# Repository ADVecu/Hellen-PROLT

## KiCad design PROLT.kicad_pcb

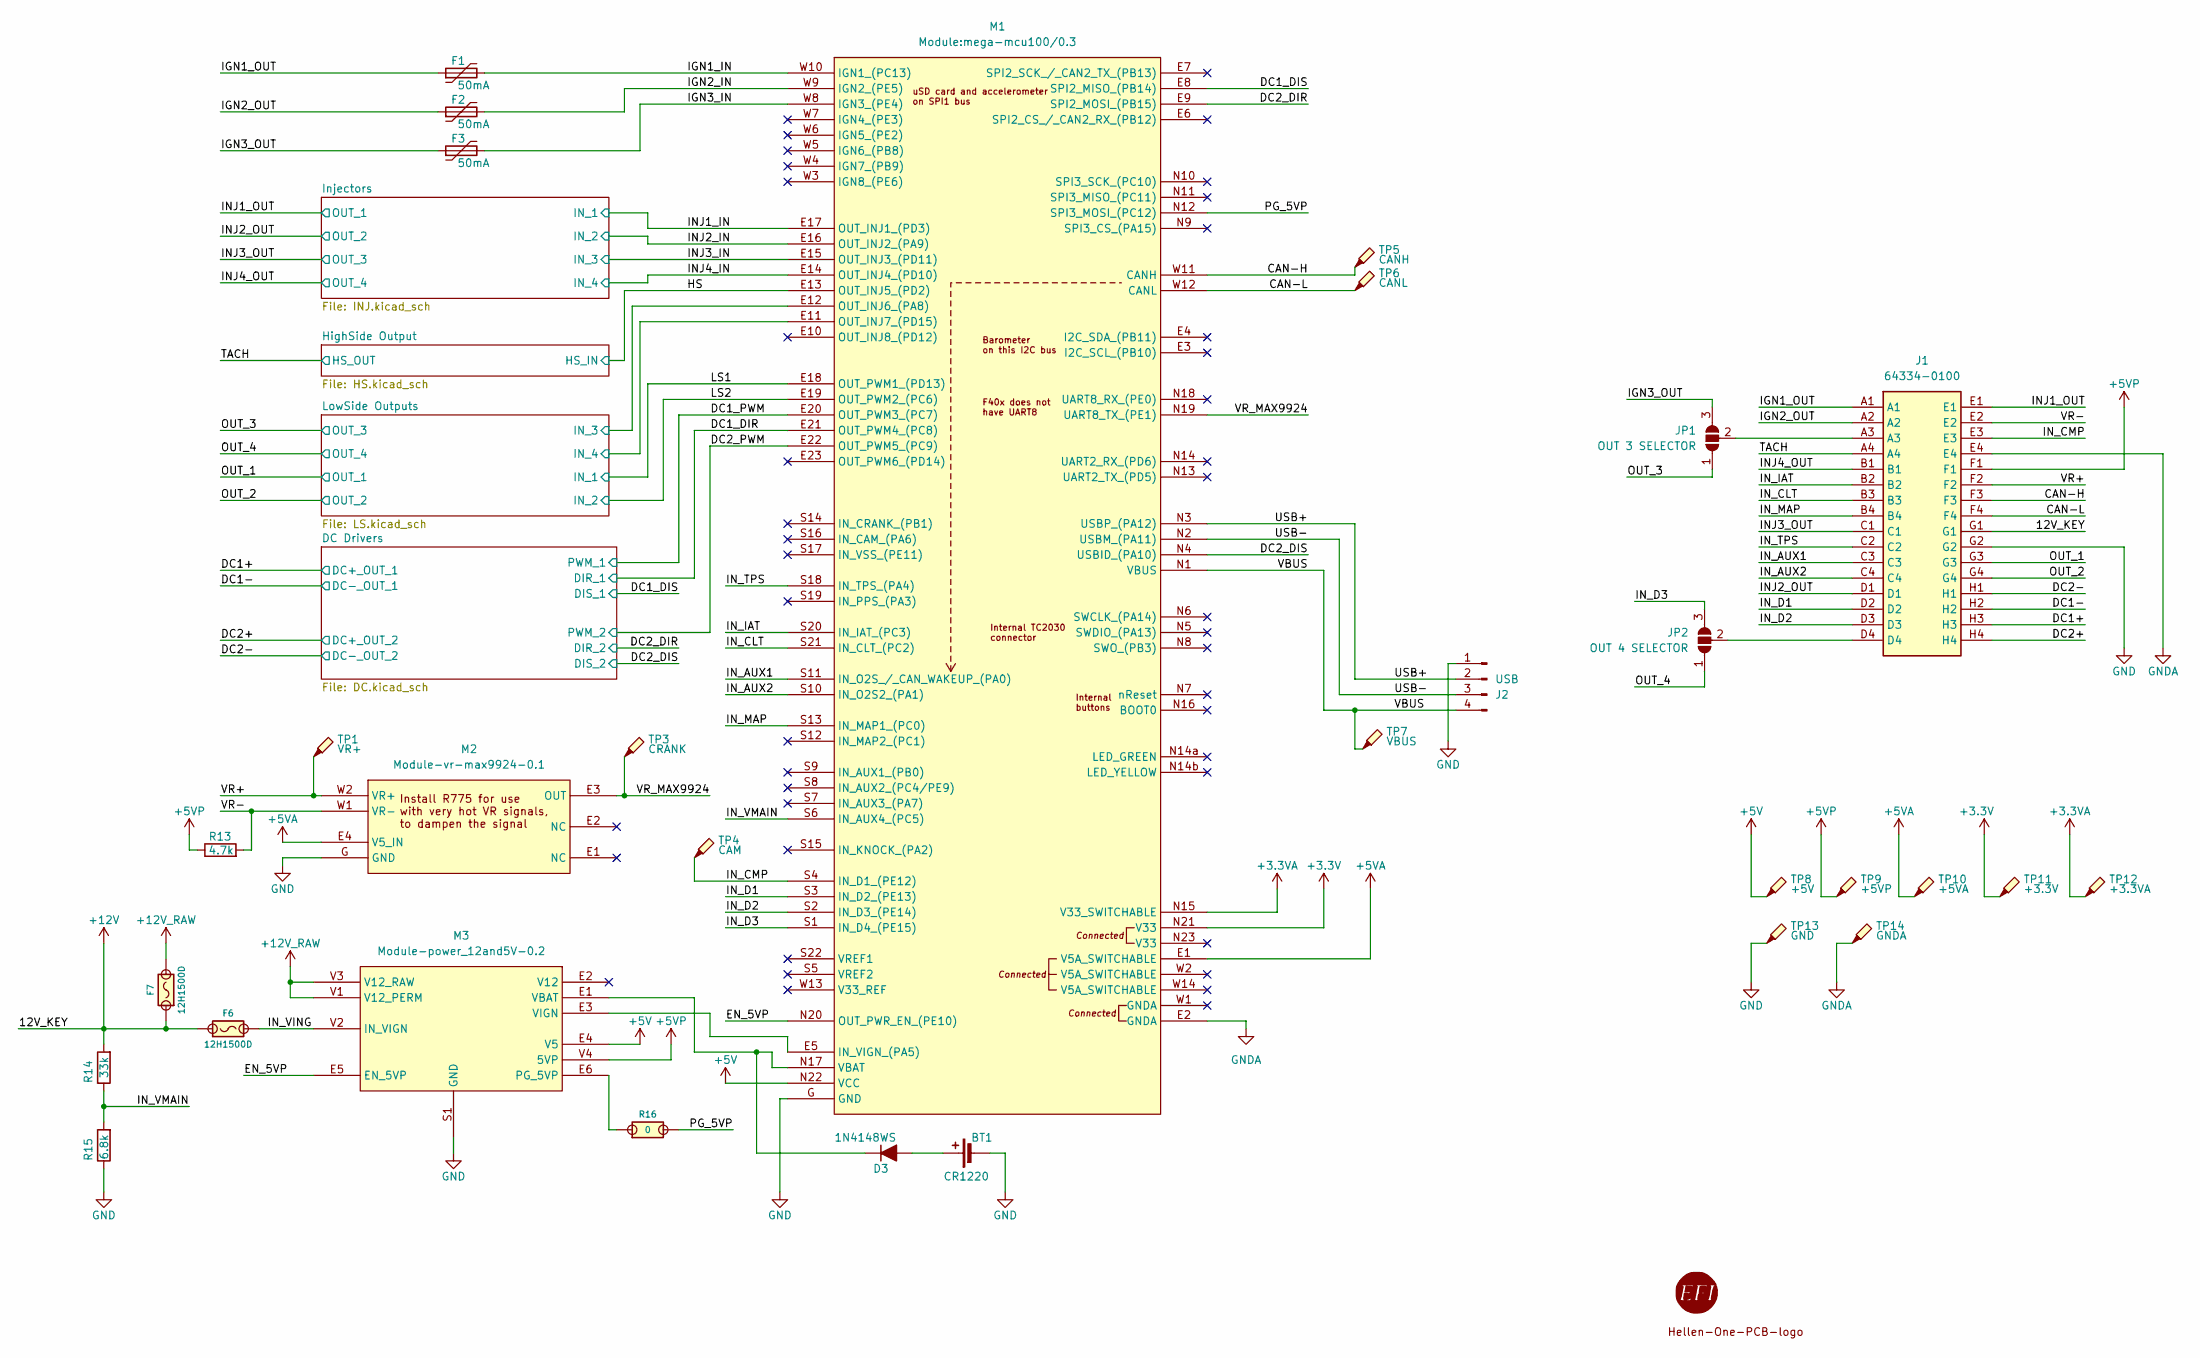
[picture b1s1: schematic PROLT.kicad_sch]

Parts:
BT1: CR1220; CR1220-2; LCSC C70381
D3: 1N4148WS; SOD-323; LCSC C2128
F1, F2, F3: 50mA; Fuse_0603_1608Metric; LCSC C369141
F6, F7: 12H1500D; PAD-1206-PAD; LCSC C182446
G1: RUSEFI_LOGO; rusefi_logo
G2: LOGO
J1: 64334-0100; 643340100; Mouser Part Number 538-64334-0100
J2: USB; JST_PH_B4B-PH-K_1x04_P2.00mm_Vertical; LCSC C5305780
JP1: OUT 3 SELECTOR; SolderJumper-3_P2.0mm_Open_TrianglePad1.0x1.5mm
JP2: OUT 4 SELECTOR; SolderJumper-3_P2.0mm_Open_TrianglePad1.0x1.5mm
M1: Module:mega-mcu100/0.3; mega-mcu100
M2: Module-vr-max9924-0.1; vr-max9924
M3: Module-power_12and5V-0.2; power_12and5V
R13: 4.7k; R0603; LCSC C23162
R14: 33k; R0603; LCSC C4216
R15: 6.8k; R0603; LCSC C23212
R16: 0; PAD-0805-PAD; LCSC C17477
TP1: VR+; TestPoint_Pad_D1.0mm
TP3: CRANK; TestPoint_Pad_D1.0mm
TP4: CAM; TestPoint_Pad_D1.0mm
TP5: CANH; TestPoint_Pad_D1.0mm
TP6: CANL; TestPoint_Pad_D1.0mm
TP7: VBUS; TestPoint_Pad_D1.0mm
TP8: +5V; TestPoint_Pad_D1.0mm
TP9: +5VP; TestPoint_Pad_D1.0mm
TP10: +5VA; TestPoint_Pad_D1.0mm
TP11: +3.3V; TestPoint_Pad_D1.0mm
TP12: +3.3VA; TestPoint_Pad_D1.0mm
TP13: GND; TestPoint_Pad_D2.0mm
TP14: GNDA; TestPoint_Pad_D1.0mm

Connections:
+3.3V: M1.N21 (V33), TP11.1; also elsewhere on the board
+3.3VA: M1.N15 (V33_SWITCHABLE), TP12.1
+5V: M1.N22 (VCC), M3.E4 (V5), TP8.1
+5VA: M1.E1 (V5A_SWITCHABLE), M2.E4 (V5_IN), TP10.1
+5VP: J1.F1, M3.V4 (5VP), R13.1, TP9.1
+12V: F6.1, F7.1, J1.G1, R14.2; also elsewhere on the board
+12V_RAW: F7.2, M3.V1 (V12_PERM), M3.V3 (V12_RAW); also elsewhere on the board
/CAN-H: J1.F3, M1.W11 (CANH), TP5.1
/CAN-L: J1.F4, M1.W12 (CANL), TP6.1
/DC1+: J1.H3; also elsewhere on the board
/DC1-: J1.H2; also elsewhere on the board
/DC1_DIR: M1.E21 (OUT_PWM4_(PC8)); also elsewhere on the board
/DC1_DIS: M1.E8 (SPI2_MISO_(PB14)); also elsewhere on the board
/DC1_PWM: M1.E20 (OUT_PWM3_(PC7)); also elsewhere on the board
/DC2+: J1.H4; also elsewhere on the board
/DC2-: J1.H1; also elsewhere on the board
/DC2_DIR: M1.E9 (SPI2_MOSI_(PB15)); also elsewhere on the board
/DC2_DIS: M1.N4 (USBID_(PA10)); also elsewhere on the board
/DC2_PWM: M1.E22 (OUT_PWM5_(PC9)); also elsewhere on the board
/EN_5VP: M1.N20 (OUT_PWR_EN_(PE10)), M3.E5 (EN_5VP)
/HS: M1.E13 (OUT_INJ5_(PD2)); also elsewhere on the board
/IGN1_IN: F1.2, M1.W10 (IGN1_(PC13))
/IGN1_OUT: F1.1, J1.A1
/IGN2_IN: F2.2, M1.W9 (IGN2_(PE5))
/IGN2_OUT: F2.1, J1.A2
/IGN3_IN: F3.2, M1.W8 (IGN3_(PE4))
/IGN3_OUT: F3.1, JP1.3 (B)
/INJ1_IN: M1.E17 (OUT_INJ1_(PD3)); also elsewhere on the board
/INJ1_OUT: J1.E1; also elsewhere on the board
/INJ2_IN: M1.E16 (OUT_INJ2_(PA9)); also elsewhere on the board
/INJ2_OUT: J1.D1; also elsewhere on the board
/INJ3_IN: M1.E15 (OUT_INJ3_(PD11)); also elsewhere on the board
/INJ3_OUT: J1.C1; also elsewhere on the board
/INJ4_IN: M1.E14 (OUT_INJ4_(PD10)); also elsewhere on the board
/INJ4_OUT: J1.B1; also elsewhere on the board
/IN_AUX1: J1.C3, M1.S11 (IN_O2S_/_CAN_WAKEUP_(PA0))
/IN_AUX2: J1.C4, M1.S10 (IN_O2S2_(PA1))
/IN_CLT: J1.B3, M1.S21 (IN_CLT_(PC2))
/IN_CMP: J1.E3, M1.S4 (IN_D1_(PE12)), TP4.1
/IN_D1: J1.D2, M1.S3 (IN_D2_(PE13))
/IN_D2: J1.D3, M1.S2 (IN_D3_(PE14))
/IN_D3: JP2.3 (B), M1.S1 (IN_D4_(PE15))
/IN_IAT: J1.B2, M1.S20 (IN_IAT_(PC3))
/IN_MAP: J1.B4, M1.S13 (IN_MAP1_(PC0))
/IN_TPS: J1.C2, M1.S18 (IN_TPS_(PA4))
/IN_VING: F6.2, M3.V2 (IN_VIGN)
/IN_VMAIN: M1.S6 (IN_AUX4_(PC5)), R14.1, R15.2
/LS1: M1.E18 (OUT_PWM1_(PD13)); also elsewhere on the board
/LS2: M1.E19 (OUT_PWM2_(PC6)); also elsewhere on the board
/LowSide Outputs/IN_3: M1.E12 (OUT_INJ6_(PA8)); also elsewhere on the board
/LowSide Outputs/IN_4: M1.E11 (OUT_INJ7_(PD15)); also elsewhere on the board
/OUT_1: J1.G3; also elsewhere on the board
/OUT_2: J1.G4; also elsewhere on the board
/OUT_3: JP1.1 (A); also elsewhere on the board
/OUT_4: JP2.1 (A); also elsewhere on the board
/PG_5VP: M1.N12 (SPI3_MOSI_(PC12)), R16.2
/TACH: J1.A4; also elsewhere on the board
/USB+: J2.2, M1.N3 (USBP_(PA12))
/USB-: J2.3, M1.N2 (USBM_(PA11))
/VBUS: J2.4, M1.N1 (VBUS), TP7.1
/VR+: J1.F2, M2.W2 (VR+), TP1.1
/VR-: J1.E2, M2.W1 (VR-), R13.2
/VR_MAX9924: M1.N19 (UART8_TX_(PE1)), M2.E3 (OUT), TP3.1
GND: BT1.2 (-), J1.G2, J2.1, M1.G (GND), M2.G (GND), M3.S1 (GND), R15.1, TP13.1; also elsewhere on the board
GNDA: J1.E4, M1.E2 (GNDA), TP14.1
unnamed: BT1.1 (+), D3.2 (A)
unnamed: D3.1 (K), M1.N17 (VBAT), M3.E1 (VBAT)
unnamed: J1.A3, JP1.2 (C)
unnamed: J1.D4, JP2.2 (C)
unnamed: M1.E5 (IN_VIGN_(PA5)), M3.E3 (VIGN)
unnamed: M3.E6 (PG_5VP), R16.1

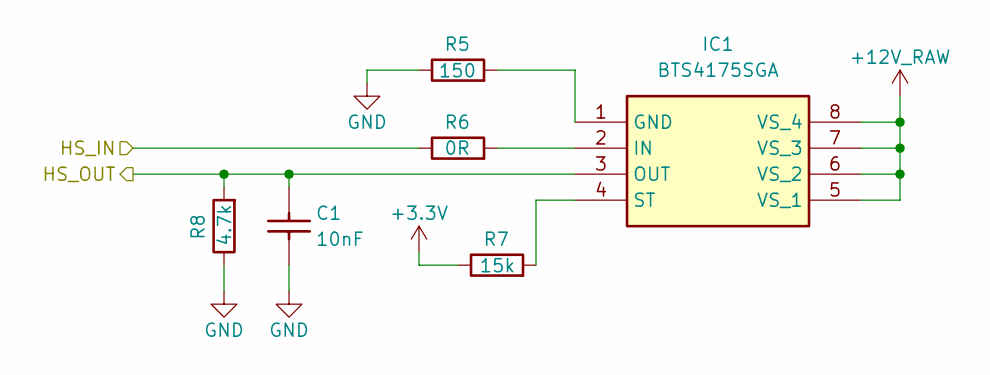
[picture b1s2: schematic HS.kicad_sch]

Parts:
C1: 10nF; C0603; LCSC C57112
IC1: BTS4175SGA; SOIC127P600X175-8N; Mouser Part Number 726-BTS4175SGA
R5: 150; R0603; LCSC C325755
R6: 0R; R0603; LCSC C2770782
R7: 15k; R0603; LCSC C881094
R8: 4.7k; R0603; LCSC C23162

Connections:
+3.3V: R7.1; also elsewhere on the board
+12V_RAW: IC1.5 (VS_1), IC1.6 (VS_2), IC1.7 (VS_3), IC1.8 (VS_4); also elsewhere on the board
/HS: R6.1; also elsewhere on the board
/TACH: C1.2, IC1.3 (OUT), R8.2; also elsewhere on the board
GND: C1.1, R5.1, R8.1; also elsewhere on the board
unnamed: IC1.1 (GND), R5.2
unnamed: IC1.2 (IN), R6.2
unnamed: IC1.4 (ST), R7.2

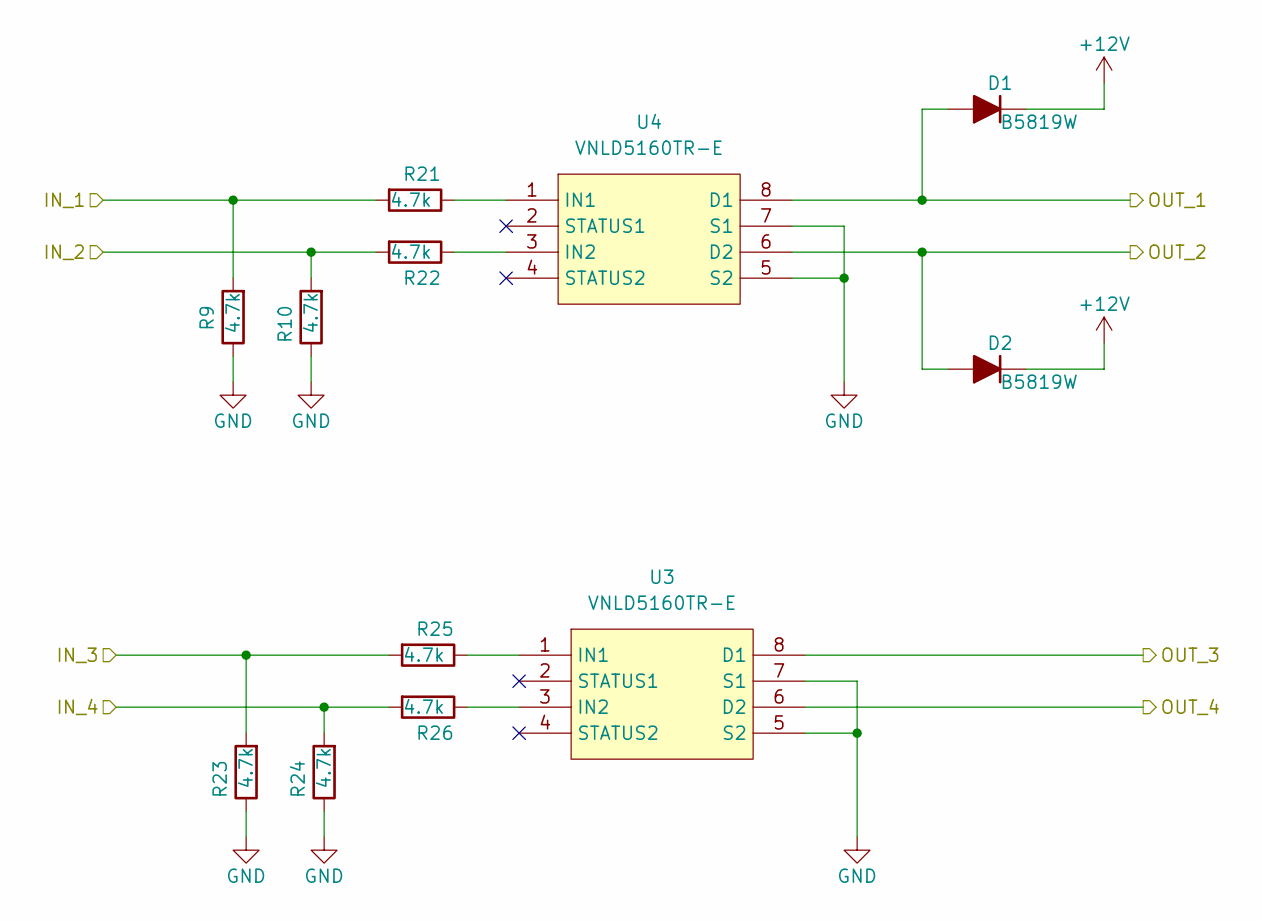
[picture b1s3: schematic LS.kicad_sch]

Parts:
D1, D2: B5819W; SOD-123; LCSC C8598
R9, R10, R21, R22, R23, R24, R25, R26: 4.7k; R0603; LCSC C23162
U3, U4: VNLD5160TR-E; SOIC-8_3.9x4.9mm_P1.27mm; LCSC C377942

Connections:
+12V: D1.1 (K), D2.1 (K); also elsewhere on the board
/LS1: R9.2, R21.2; also elsewhere on the board
/LS2: R10.2, R22.2; also elsewhere on the board
/LowSide Outputs/IN_3: R23.2, R25.2; also elsewhere on the board
/LowSide Outputs/IN_4: R24.2, R26.2; also elsewhere on the board
/OUT_1: D1.2 (A), U4.8 (D1); also elsewhere on the board
/OUT_2: D2.2 (A), U4.6 (D2); also elsewhere on the board
/OUT_3: U3.8 (D1); also elsewhere on the board
/OUT_4: U3.6 (D2); also elsewhere on the board
GND: R9.1, R10.1, R23.1, R24.1, U3.5 (S2), U3.7 (S1), U4.5 (S2), U4.7 (S1); also elsewhere on the board
unnamed: R25.1, U3.1 (IN1)
unnamed: R26.1, U3.3 (IN2)
unnamed: R21.1, U4.1 (IN1)
unnamed: R22.1, U4.3 (IN2)

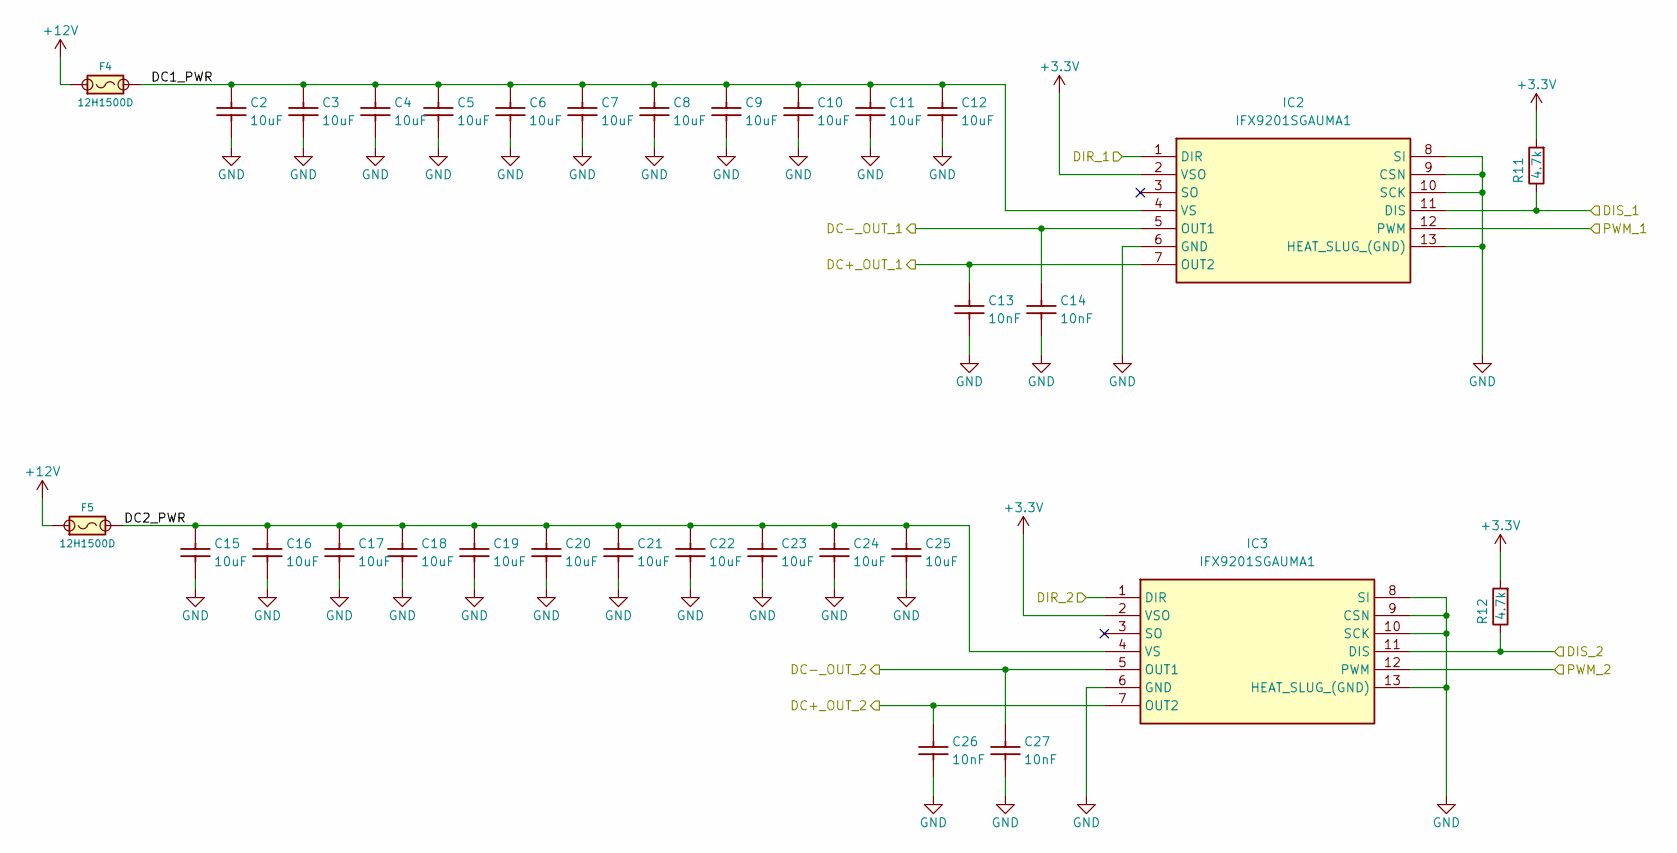
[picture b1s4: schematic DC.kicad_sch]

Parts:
C2, C3, C4, C5, C6, C7, C8, C9, C10, C11, C12, C15, C16, C17, C18, C19, C20, C21, C22, C23, C24, C25: 10uF; C0805; LCSC C15850
C13, C14, C26, C27: 10nF; C0603; LCSC C57112
F4, F5: 12H1500D; PAD-1206-PAD; LCSC C182446
IC2, IC3: IFX9201SGAUMA1; PG-DSO-12-17; Mouser Part Number 726-IFX9201SGAUMA1
R11, R12: 4.7k; R0603; LCSC C23162

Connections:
+3.3V: IC2.2 (VSO), IC3.2 (VSO), R11.2, R12.2; also elsewhere on the board
+12V: F4.1, F5.1; also elsewhere on the board
/DC1+: C13.2, IC2.7 (OUT2); also elsewhere on the board
/DC1-: C14.2, IC2.5 (OUT1); also elsewhere on the board
/DC1_DIR: IC2.1 (DIR); also elsewhere on the board
/DC1_DIS: IC2.11 (DIS), R11.1; also elsewhere on the board
/DC1_PWM: IC2.12 (PWM); also elsewhere on the board
/DC2+: C26.2, IC3.7 (OUT2); also elsewhere on the board
/DC2-: C27.2, IC3.5 (OUT1); also elsewhere on the board
/DC2_DIR: IC3.1 (DIR); also elsewhere on the board
/DC2_DIS: IC3.11 (DIS), R12.1; also elsewhere on the board
/DC2_PWM: IC3.12 (PWM); also elsewhere on the board
/DC Drivers/DC1_PWR: C2.2, C3.2, C4.2, C5.2, C6.2, C7.2, C8.2, C9.2, C10.2, C11.2, C12.2, F4.2, IC2.4 (VS)
/DC Drivers/DC2_PWR: C15.2, C16.2, C17.2, C18.2, C19.2, C20.2, C21.2, C22.2, C23.2, C24.2, C25.2, F5.2, IC3.4 (VS)
GND: C2.1, C3.1, C4.1, C5.1, C6.1, C7.1, C8.1, C9.1, C10.1, C11.1, C12.1, C13.1, C14.1, C15.1, C16.1, C17.1, C18.1, C19.1, C20.1, C21.1, C22.1, C23.1, C24.1, C25.1, C26.1, C27.1, IC2.6 (GND), IC2.8 (SI), IC2.9 (CSN), IC2.10 (SCK), IC2.13 (HEAT_SLUG_(GND)), IC3.6 (GND), IC3.8 (SI), IC3.9 (CSN), IC3.10 (SCK), IC3.13 (HEAT_SLUG_(GND)); also elsewhere on the board

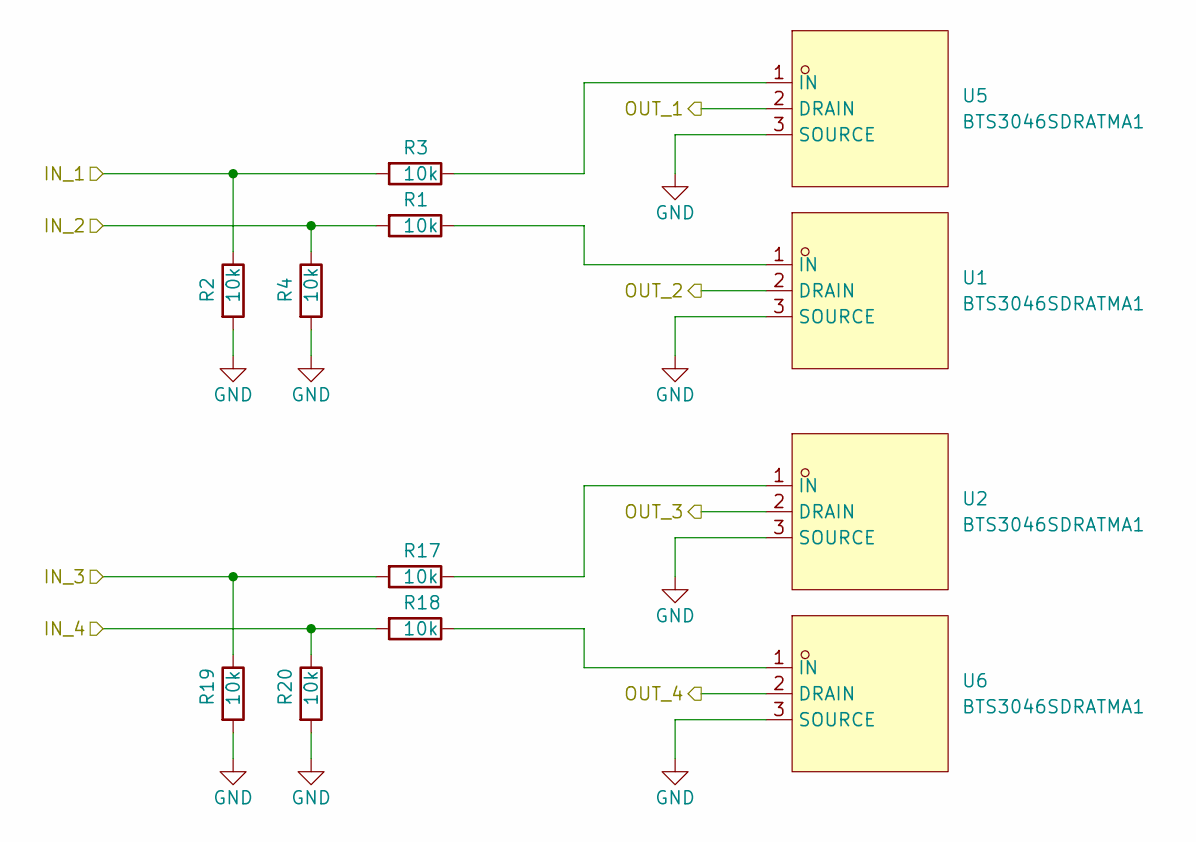
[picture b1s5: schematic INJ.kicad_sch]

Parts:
R1, R2, R3, R4, R17, R18, R19, R20: 10k; R0603; LCSC C98220
U1, U2, U5, U6: BTS3046SDRATMA1; PG-TO252-3_L6.5-W6.2-P4.57-LS10.0-BR-CW-1; MPN BTS3046SDRATMA1; LCSC Part C2680440

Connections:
/INJ1_IN: R2.1, R3.2; also elsewhere on the board
/INJ1_OUT: U5.2 (DRAIN); also elsewhere on the board
/INJ2_IN: R1.2, R4.1; also elsewhere on the board
/INJ2_OUT: U1.2 (DRAIN); also elsewhere on the board
/INJ3_IN: R17.2, R19.1; also elsewhere on the board
/INJ3_OUT: U2.2 (DRAIN); also elsewhere on the board
/INJ4_IN: R18.2, R20.1; also elsewhere on the board
/INJ4_OUT: U6.2 (DRAIN); also elsewhere on the board
GND: R2.2, R4.2, R19.2, R20.2, U1.3 (SOURCE), U2.3 (SOURCE), U5.3 (SOURCE), U6.3 (SOURCE); also elsewhere on the board
unnamed: R1.1, U1.1 (IN)
unnamed: R17.1, U2.1 (IN)
unnamed: R3.1, U5.1 (IN)
unnamed: R18.1, U6.1 (IN)

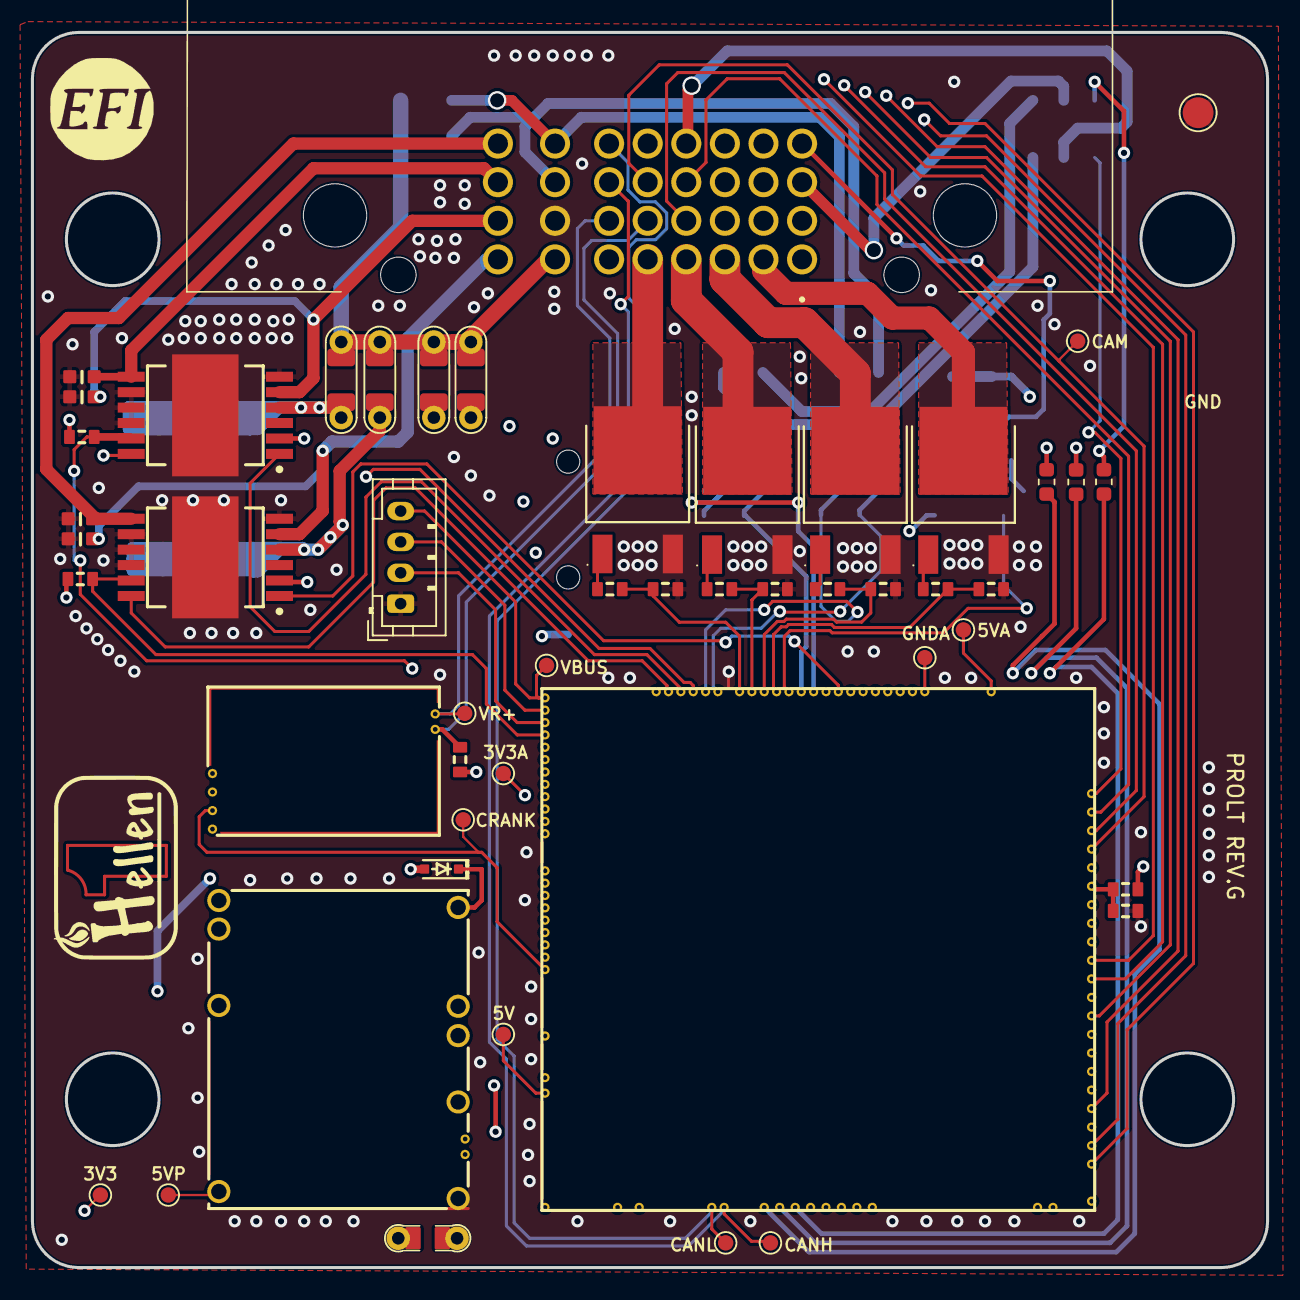
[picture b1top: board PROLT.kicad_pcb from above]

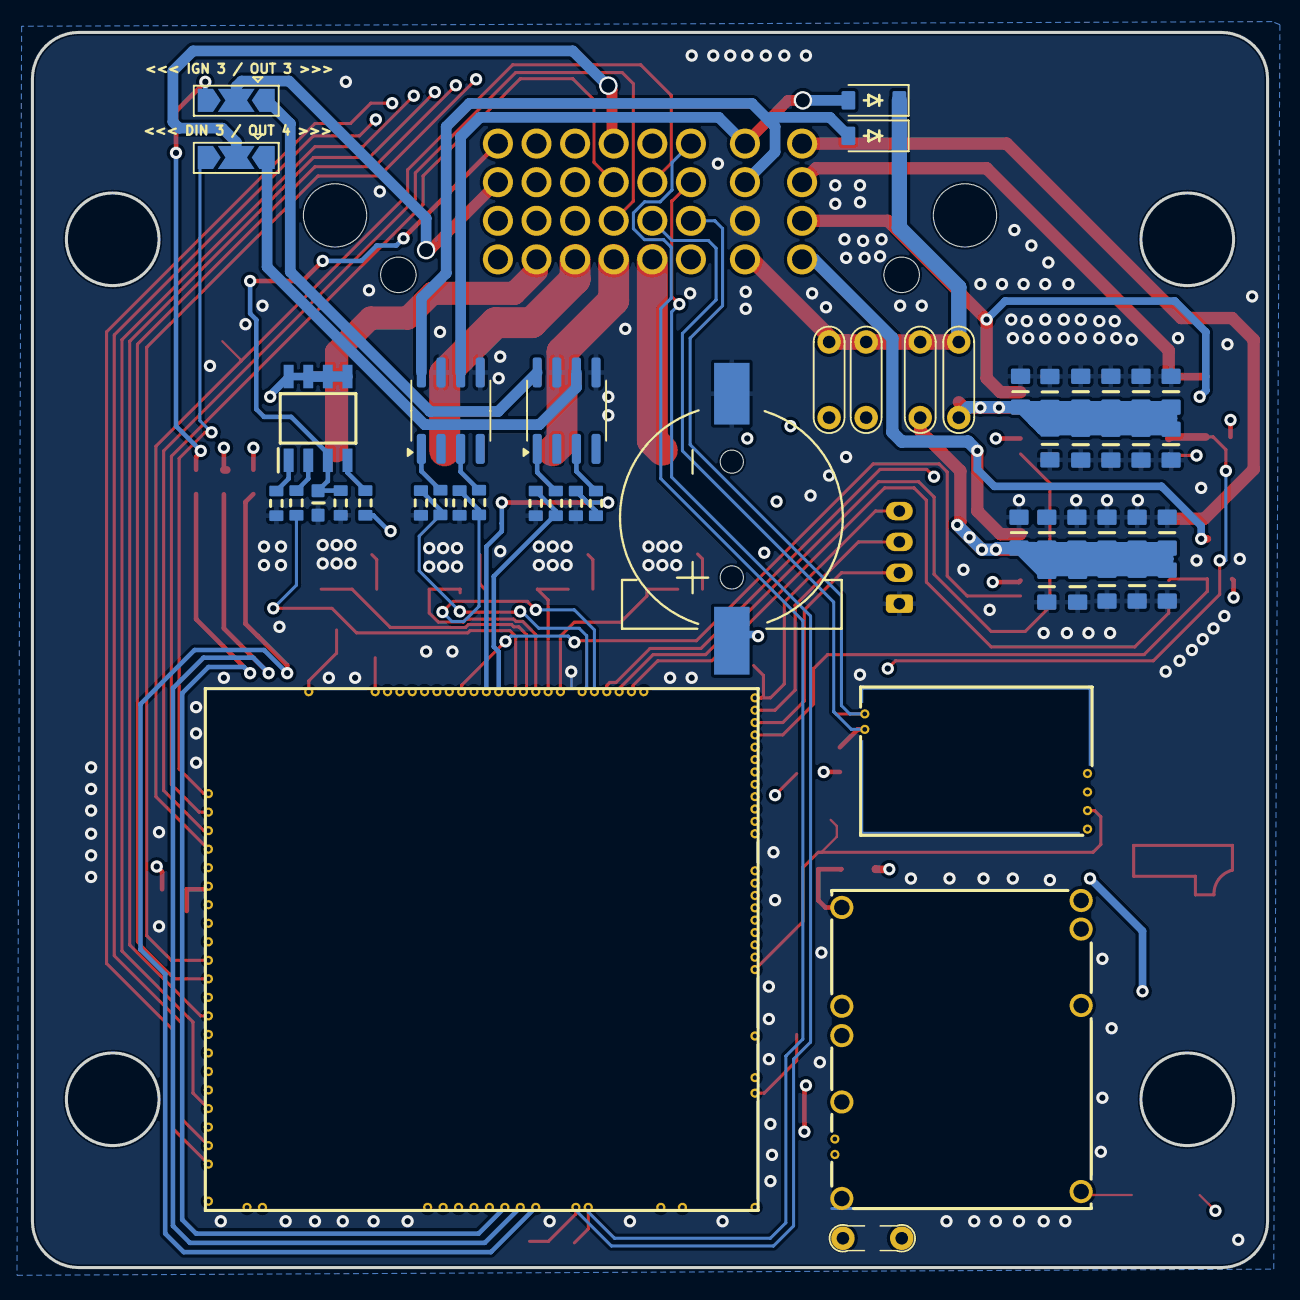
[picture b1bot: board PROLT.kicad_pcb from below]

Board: 4 copper layers, 80.0 x 80.0 mm, 95 parts (43 on the bottom side), 84 nets.

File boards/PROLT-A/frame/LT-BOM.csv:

Comment,Designator,Footprint,LCSC Part #
"CR1220","BT1","CR1220-2","C70381"
"10nF","C1","C0603","C57112"
"10uF","C2","C0805","C15850"
"10uF","C3","C0805","C15850"
"10uF","C4","C0805","C15850"
"10uF","C5","C0805","C15850"
"10uF","C6","C0805","C15850"
"10uF","C7","C0805","C15850"
"10uF","C8","C0805","C15850"
"10uF","C9","C0805","C15850"
"10uF","C10","C0805","C15850"
"10uF","C11","C0805","C15850"
"10uF","C12","C0805","C15850"
"10nF","C13","C0603","C57112"
"10nF","C14","C0603","C57112"
"10uF","C15","C0805","C15850"
"10uF","C16","C0805","C15850"
"10uF","C17","C0805","C15850"
"10uF","C18","C0805","C15850"
"10uF","C19","C0805","C15850"
"10uF","C20","C0805","C15850"
"10uF","C21","C0805","C15850"
"10uF","C22","C0805","C15850"
"10uF","C23","C0805","C15850"
"10uF","C24","C0805","C15850"
"10uF","C25","C0805","C15850"
"10nF","C26","C0603","C57112"
"10nF","C27","C0603","C57112"
"100n","C28","C0603","C14663"
"B5819W","D1","SOD-123","C8598"
"B5819W","D2","SOD-123","C8598"
"1N4148WS","D3","SOD-323","C2128"
"50mA","F1","Fuse_0603_1608Metric","C369141"
"50mA","F2","Fuse_0603_1608Metric","C369141"
"50mA","F3","Fuse_0603_1608Metric","C369141"
"12H1500D","F4","PAD-1206-PAD","C182446"
"12H1500D","F5","PAD-1206-PAD","C182446"
"12H1500D","F6","PAD-1206-PAD","C182446"
"12H1500D","F7","PAD-1206-PAD","C182446"
"RUSEFI_LOGO","G1","rusefi_logo",""
"LOGO","G2","LOGO",""
"BTS4175SGA","IC1","SOIC127P600X175-8N","C152451"
"IFX9201SGAUMA1","IC2","PG-DSO-12-17","C112633"
"IFX9201SGAUMA1","IC3","PG-DSO-12-17","C112633"
"64334-0100","J1","643340100","C293657"
"USB","J2","JST_PH_B4B-PH-K_1x04_P2.00mm_Vertical","C5305780"
"Module:mega-mcu100/0.3","M1","mega-mcu100",""
"Module:vr-max9924/0.1","M2","vr-max9924",""
"Module:power_12and5V/0.2","M3","power_12and5V",""
"4.7k","R1","R0603","C23162"
"4.7k","R2","R0603","C23162"
"4.7k","R3","R0603","C23162"
"4.7k","R4","R0603","C23162"
"150","R5","R0603","C325755"
"0R","R6","R0603","C2770782"
"15k","R7","R0603","C881094"
"4.7k","R8","R0603","C23162"
"4.7k","R9","R0603","C23162"
"4.7k","R10","R0603","C23162"
"4.7k","R11","R0603","C23162"
"4.7k","R12","R0603","C23162"
"4.7k","R13","R0603","C23162"
"33k","R14","R0603","C4216"
"6.8k","R15","R0603","C23212"
"0","R16","PAD-0805-PAD","C17477"
"VR+","TP1","TestPoint_Pad_D1.0mm",""
"CRANK","TP3","TestPoint_Pad_D1.0mm",""
"CAM","TP4","TestPoint_Pad_D1.0mm",""
"CANH","TP5","TestPoint_Pad_D1.0mm",""
"CANL","TP6","TestPoint_Pad_D1.0mm",""
"VBUS","TP7","TestPoint_Pad_D1.0mm",""
"+5V","TP8","TestPoint_Pad_D1.0mm",""
"+5VP","TP9","TestPoint_Pad_D1.0mm",""
"+5VA","TP10","TestPoint_Pad_D1.0mm",""
"+3.3V","TP11","TestPoint_Pad_D1.0mm",""
"+3.3VA","TP12","TestPoint_Pad_D1.0mm",""
"GND","TP13","TestPoint_Pad_D2.0mm",""
"GNDA","TP14","TestPoint_Pad_D1.0mm",""
"JDY-33","U1","JDY-33","C9900001612"
"VNLD5160TR-E","U2","SO8","C377942"
"VNLD5160TR-E","U3","SO8","C377942"
"VNLD5160TR-E","U4","SO8","C377942"

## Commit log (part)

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2024-05-29 Rev A
2024-05-29 [skip actions] Auto-generated board v2.1
2024-06-02 GHA says update kicad6-libraries
2024-06-04 GHA says update hellen-one
2024-07-20 Rev A - New Bom-Remplace, fix HS resistors
2024-07-20 Rev A - Fix LEDS, MAX9924UAUB+T
2024-07-20 Rev A - DNP J1-J2
2025-09-04 Rev B
2025-10-07 Stupid mistake — I ended up making a voltage divider instead of a protection circuit. I'm the best.
2025-11-11 Rev D
2026-01-01 Rev E
    Back to VNLD5160TR-E, 1 channel per injector now
2026-02-24 REV-F
